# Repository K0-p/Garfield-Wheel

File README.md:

# Garfield Wheel

### HID-compliant (and Garfield-themed) game controller with embedded button mapping firmware and gyroscope controls
###### *Designed to run on the TM4C*

Developed by Gabriel Moore and Calvin Heischman

[Spring 2024 finalist for ECE445L at UT Austin](https://github.com/ECE445L/ECE445L-Winners/tree/main)

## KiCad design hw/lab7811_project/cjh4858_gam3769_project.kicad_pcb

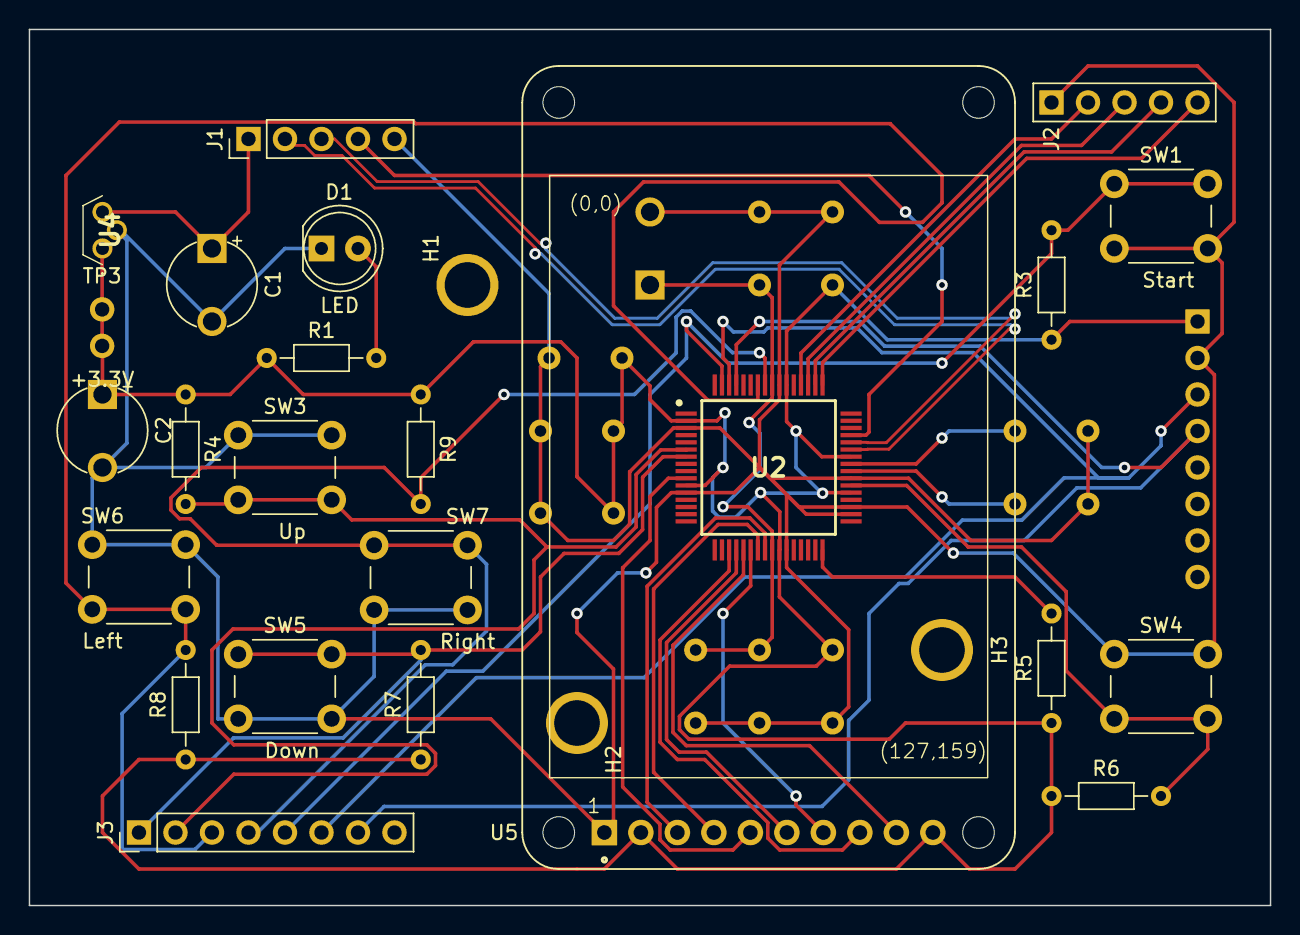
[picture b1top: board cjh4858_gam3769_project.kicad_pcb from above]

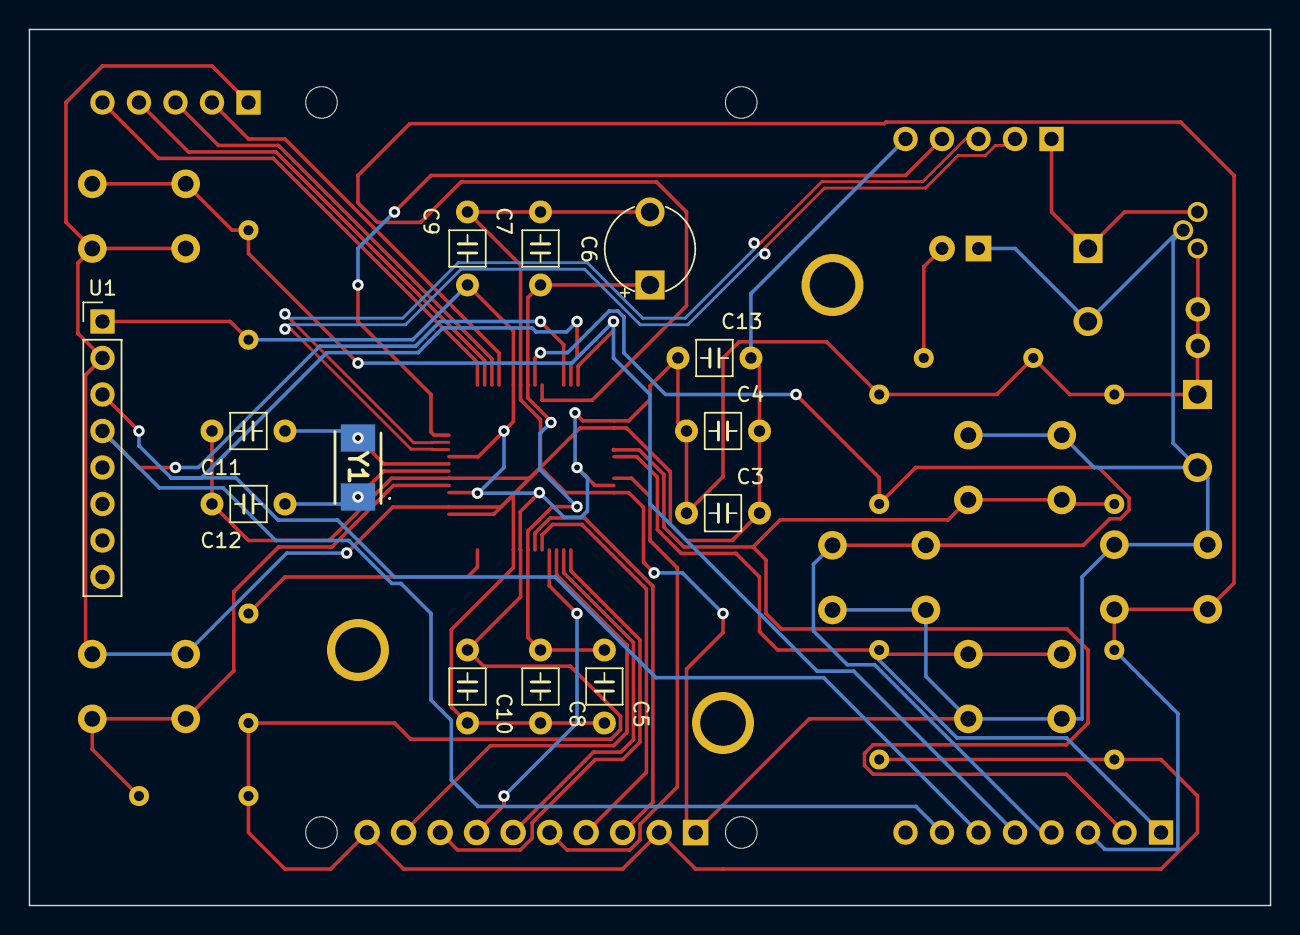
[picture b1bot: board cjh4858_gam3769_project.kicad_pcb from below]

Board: 2 copper layers, 86.4 x 61.0 mm, 40 parts (13 on the bottom side), 30 nets.

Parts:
C1, C2: 4.7uF; CP_Radial_Tantal200mil
C3, C10: 0.01uF; C_Axial_200mil
C4, C7, C8, C9: 0.1uF; C_Axial_200mil
C5, C13: 1uF; C_Axial_200mil
C6: 2.2uF; CP_Radial_Tantal200mil
C11, C12: 10pF C0G; C_Axial_200mil
D1: LED; LED_D5.0mm
H1, H2, H3: MountingHole_4_40
J1: Conn_01x05; PinHeader_1x05_P2.54mm_Vertical
J2: JTAG; PinHeader_1x05_P2.54mm_Vertical
J3: Conn_01x08_Pin; PinHeader_1x08_P2.54mm_Vertical
R1: 470; R_Axial_DIN0204_L3.6mm_D1.6mm_P7.62mm_Horizontal
R3, R4, R6, R7, R8, R9: 10k; R_Axial_DIN0204_L3.6mm_D1.6mm_P7.62mm_Horizontal
R5: 1M; R_Axial_DIN0204_L3.6mm_D1.6mm_P7.62mm_Horizontal
SW1: Start; SW_PUSH_6mm
SW3: Up; SW_PUSH_6mm
SW4: Reset; SW_PUSH_6mm
SW5: Down; SW_PUSH_6mm
SW6: Left; SW_PUSH_6mm
SW7: Right; SW_PUSH_6mm
TP3: +3.3V; Testpoint_1x02_P2.54mm
U1: MPU-6050; PinHeader_1x08_P2.54mm_Vertical
U2: TM4C123GH6PMIR; QFP50P1200X1200X160-64N
U4: LP2950-33LPRE3; TL431CLPM
U5: Adafruit ST7735R; adafruit_st7735r2
Y1: ABM3-16.000MHZ-B2-T; ABM3

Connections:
+3V3: C2.1, C3.1, C4.1, C9.1, C10.1, C13.1, R1.1, R3.1, R4.1, R5.1, R6.1, R7.1, R8.1, R9.1, TP3.1 (A), TP3.2 (B), U1.1 (CLKIN), U2.2 (VDDA), U2.11 (VDD_1), U2.26 (VDD_2), U2.37 (VBAT), U2.42 (VDD_3), U2.54 (VDD_4), U4.1 (OUTPUT), U5.2 (VCC), U5.10 (LITE)
/LDO: C5.1, C6.1, C7.1, C8.1, U2.25 (VDDC_1), U2.56 (VDDC_2)
/OSC1: C11.1, U2.41 (OSC1), Y1.2
/OSC2: C12.1, U2.40 (OSC0), Y1.1
/Reset: R6.2, SW4.2, U2.38 (~RST)
/TCK: J2.2 (B), U2.52 (PC0/TCK/SWCLK)
/TDI: J2.4 (C), U2.50 (PC2/TDI)
/TDO: J2.5 (C), U2.49 (PC3/TDO/SWO)
/TMS: J2.3 (C), U2.51 (PC1/TMS/SWDIO)
D+: J1.3, U2.44 (PD5)
D-: J1.2, U2.43 (PD4)
GND: C1.2, C2.2, C3.2, C4.2, C5.2, C6.2, C7.2, C8.2, C9.2, C10.2, C11.2, C12.2, C13.2, D1.1 (K), J1.5, J2.1 (A), SW1.2, SW3.1, SW4.1, SW5.2, SW6.1, SW7.2, U1.2 (NC), U2.3 (GNDA), U2.12 (GND_1), U2.27 (GND_2), U2.34 (XOSC0), U2.35 (GNDX), U2.39 (GND_3), U2.55 (GND_4), U4.2 (GND), U5.1 (GND)
unnamed: D1.2 (A), R1.2
unnamed: C1.1, J1.1, U4.3 (INPUT)
unnamed: R5.2, U2.32 (~WAKE)
PA2: U2.19 (PA2/SSI0C1K), U5.8 (SCK)
PA3: U2.20 (PA3/SSI0FSS), U5.6 (TFT_CS)
PA4: U2.21 (PA4/SSI0RX), U5.9 (MISO)
PA5: U2.22 (PA5/SSI0TX), U5.7 (MOSI)
PA6: U2.23 (PA6), U5.4 (D/C)
PA7: U2.24 (PA7), U5.3 (RESET)
PB0: J1.4, U2.45 (PB0/USB0ID)
PB4: J3.3, R8.2, SW6.2, U2.58 (PB4)
PB5: J3.4, R9.2, SW7.1, U2.57 (PB5)
PD0: J3.7, U1.4 (NC), U2.61 (PD0)
PD1: J3.6, U1.3 (NC), U2.62 (PD1)
PD2: J3.5, R3.2, SW1.1, U2.63 (PD2)
PD7: U2.10 (PD7), U5.5 (CARD_CS)
PE2: J3.1, R7.2, SW5.1, U2.7 (PE2)
PE3: J3.2, R4.2, SW3.2, U2.6 (PE3)

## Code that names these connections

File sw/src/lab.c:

/**
 * @file        lab.c
 * @author      your name (your_email@doman.com), Jonathan Valvano, Matthew Yu
 *              <TA NAME and LAB SECTION # HERE>
 * @brief       An empty main file for running your lab.
 * @version     0.1.0
 * @date        2022-10-08 <REPLACE WITH DATE OF LAST REVISION>
 * @copyright   Copyright (c) 2022
 * @note        Potential Pinouts:
 *                  Backlight (pin 10) connected to +3.3 V
 *                  MISO (pin 9) unconnected
 *                  SCK (pin 8) connected to PA2 (SSI0Clk)
 *                  MOSI (pin 7) connected to PA5 (SSI0Tx)
 *                  TFT_CS (pin 6) connected to PA3 (SSI0Fss)
 *                  CARD_CS (pin 5) unconnected
 *                  Data/Command (pin 4) connected to PA6 (GPIO)
 *                  RESET (pin 3) connected to PA7 (GPIO)
 *                  VCC (pin 2) connected to +3.3 V
 *                  Gnd (pin 1) connected to ground
 *
 *                  Center of 10k-ohm potentiometer connected to PE2/AIN1
 *                  Bottom of 10k-ohm potentiometer connected to ground
 *                  Top of 10k-ohm potentiometer connected to +3.3V
 *
 *              Warning. Initial code for the RGB driver creates bright flashing
 *              lights. Remove this code and do not run if you have epilepsy.
 */

/** File includes. */
#include <stdint.h>

/* Register definitions. */
#include "../inc/tm4c123gh6pm.h"
/* Clocking. */
#include "../inc/PLL.h"
/* Clock delay and interrupt control. */
#include "../inc/CortexM.h"
/* Initialization of all the pins. */
#include "../inc/Unified_Port_Init.h"
/* Talking to PC via UART. */
#include "../inc/UART.h"
/* ST7735 display. */
#include "../inc/ST7735.h"

/* Add whatever else you need here! */
#include "../lib/RGB/RGB.h"
#include "gyro.h"

int main(void) {
    /* Disable interrupts for initialization. */
    DisableInterrupts();

    /* Initialize clocking. */
    PLL_Init(Bus80Mhz);

    /* Allow us to talk to the PC via PuTTy! Check device manager to see which
       COM serial port we are on. The baud rate is 115200 chars/s. */
    UART_Init(7);

    /* Initialize all ports. */
    Unified_Port_Init();

    /* Start RGB flashing. WARNING! BRIGHT FLASHING COLORS. DO NOT RUN IF YOU HAVE EPILEPSY. */
    RGBInit();

    /* Allows any enabled timers to begin running. */
    EnableInterrupts();

    /* Print starting message to the PC and the ST7735. */
    ST7735_FillScreen(ST7735_BLACK);
    ST7735_SetCursor(0, 0);
    ST7735_OutString(
        "ECE445L Final lab.\n"
        "Press SW1 to start.\n");
    UART_OutString(
        "ECE445L Final lab.\r\n"
        "Press SW1 to start.\r\n");
    Pause();

    /* Stop RGB and turn off any on LEDs. */
    RGBStop();
    PF1 = 0;
    PF2 = 0;
    PF3 = 0;

    /* Reset screen. */
    ST7735_FillScreen(ST7735_BLACK);
    ST7735_SetCursor(0, 0);
    ST7735_OutString("Starting...\n");
    UART_OutString("Starting...\r\n");

		float gvalues[6];

    while (1) {
        /* TODO: Write your code here! */
        WaitForInterrupt();
				
				//read gyro data  --  can move to interrupts later
				gvalues = gyromain();
			
				//call usb/uart handlers after having read data
				//USB();
				//UART();
    }
    return 1;
}

/** Function Implementations. */
void DelayWait10ms(uint32_t n) {
    uint32_t volatile time;
    while (n){
        time = 727240 * 2 / 91;  // 10msec
        while (time){
            --time;
        }
        --n;
    }
}

void Pause(void) {
    while (PF4 == 0x00) {
        DelayWait10ms(10);
    }
    while (PF4 == 0x10) {
        DelayWait10ms(10);
    }
}

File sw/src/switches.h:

// *    Buttons (recommended garfield kart keybind):
// *				MODE 1 [1 pulse LED]: Full controls w/ gyro
// *				MODE 2 [2 pulse LED]:	No gryo, just use left/right buttons to steer with accelerate auto on
// *			Start: PD2	(bind to forwards)
// *			Reset: RST
// *			Up:		 PE3	(TOGGLE MODE  --  only impacts the following 3 buttons)
// *			Right: PB5	1:(bind to pause) 		2:(bind to right steering)
// *			Down:	 PE2	1:(bind to backwards) 2:(bind to toggle off/forwards)
// *			Left:	 PB4	1:(bind to drift) 		2:(bind to left steering)

#include <stdbool.h>
#include <stdint.h>

extern struct buttholes_t{
	uint32_t start;
	uint32_t up;
	uint32_t right;
	uint32_t down;
	uint32_t left;
	uint32_t right_R;
	uint32_t left_L;
};

struct buttholes_t getbuttons(uint32_t portD);
uint32_t press_task(uint32_t state, uint32_t buttons);

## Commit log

2024-03-20 add deadline
2024-03-20 boom boom
2024-03-23 created project for lab 7, 8, and 11
2024-03-23 Found some files to help with UART to USB communication
2024-03-25 gyro
2024-03-25 gyro fix
2024-03-25 gyro trim
2024-03-25 combined files
2024-03-25 changing project files
2024-03-25 updated sw
2024-03-25 removing useless files
2024-03-25 docs fixed
2024-03-25 added project modules
2024-03-25 gyro issues
2024-03-27 fixing git issues
2024-03-27 gyro wip
2024-03-27 new footprints
2024-03-27 temporarily disabled USB for wip
2024-03-27 updated the schematic
2024-03-27 usb lissues
2024-03-27 usb lib
2024-03-27 usb library setup w/ bools
2024-03-27 working on usb scratch
2024-03-27 usb protocol is making me lose it, i close my eyes and see flash drives
2024-03-29 finished schematic and pcb for TA review
2024-03-29 bom and report updated
2024-03-29 gyro is stuck in a busy wait loop
2024-03-30 Feedback regarding hardware
2024-04-01 approved pcb
2024-04-10 integrating USB code
2024-04-12 integrating usb to main
2024-04-12 improved documentation and cleaned up code for garf_handler
2024-04-12 got rid of redundant #includes
2024-04-12 added wheel stl files in hw directory
2024-04-12 fixed documentation
2024-04-12 fixed button bug
2024-04-12 defined button layout and control scheme
2024-04-17 visualization, new button config, menu
2024-04-17 button polling
2024-04-18 buttons fixed, holy shit so many errors
2024-04-18 menu
2024-04-20 added the gyro stuff
2024-04-22 button fix
2024-04-25 FINAL PROJECT
2024-04-25 GARFIELD WHEEL
2024-04-26 add my hardware stuff
2024-04-26 finished report
